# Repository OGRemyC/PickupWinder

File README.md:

View this project on [CADLAB.io](https://cadlab.io/project/1237). 

# PickupWinder
Arduino code designed to run on the Digispark Pro board.

Current Features:
<ul>
<li>Basic DC motor control</li>
<li>Open loop speed control</li>
</ul>

Future Features:
<ul>
<li>Full bi-directional control via H-bridge</li>
<li>Tachometer</li>
<li>Closed-loop speed control</li>
</ul>

Possible Extended Features:
<ul>
<li>Automatic tensioner</li>
<li>Closed loop wire tensioner</li>
<li>Linear spool positioning via lead screw</li>
<li>Automatic wrap with various profiles</li>
</ul>

<h1>Installation</h1>
<h2>Windows</h2>
Follow instructions from the <a href="https://digistump.com/wiki/digispark/tutorials/connectingpro">Digistrump Wiki</a>.
In addition, download and install the <a href="https://github.com/micronucleus">Micronucleus</a> bootloader driver installer.

<h3>Key Elements</h3>
<ul>
<li>Arduino 1.6.6 or newer</li>
<li>Digistump <a href="https://github.com/digistump/DigistumpArduino/releases/download/1.6.7/DigistumpDrivers.zip">Drivers</a></li>
<li>Micronucleus driver installer</li>
</ul>

<h3>Steps</h3>
<ol>
<li>Download Digistrump drivers, micronucleus, and Arduino.
<li>Install Arduino.</li>
<li>Unzip Digistump drivers and micronucleus to the Arduino sketchbook folder.</li>
<li>Run [Sketchbook]\micronucleus-master\windows_driver_installer\zadig_2.1.2.exe</li>
<li>In Zadig select Device>Load Preset Device. </li>
<li>Select micronucleus.cfg in the same folder. </li>
</ol>

<h1>Uploading Sketches to the DigiSpark Pro</h1>
Open \\PickupWinder\digiProPickupWinder\digiProPickupWinder.ino in the Arduino IDE.
Select "Digispark Pro (Default 16 MHz)" from Tools>Board:
Start click Upload.
Connect the DigiSpark board via USB

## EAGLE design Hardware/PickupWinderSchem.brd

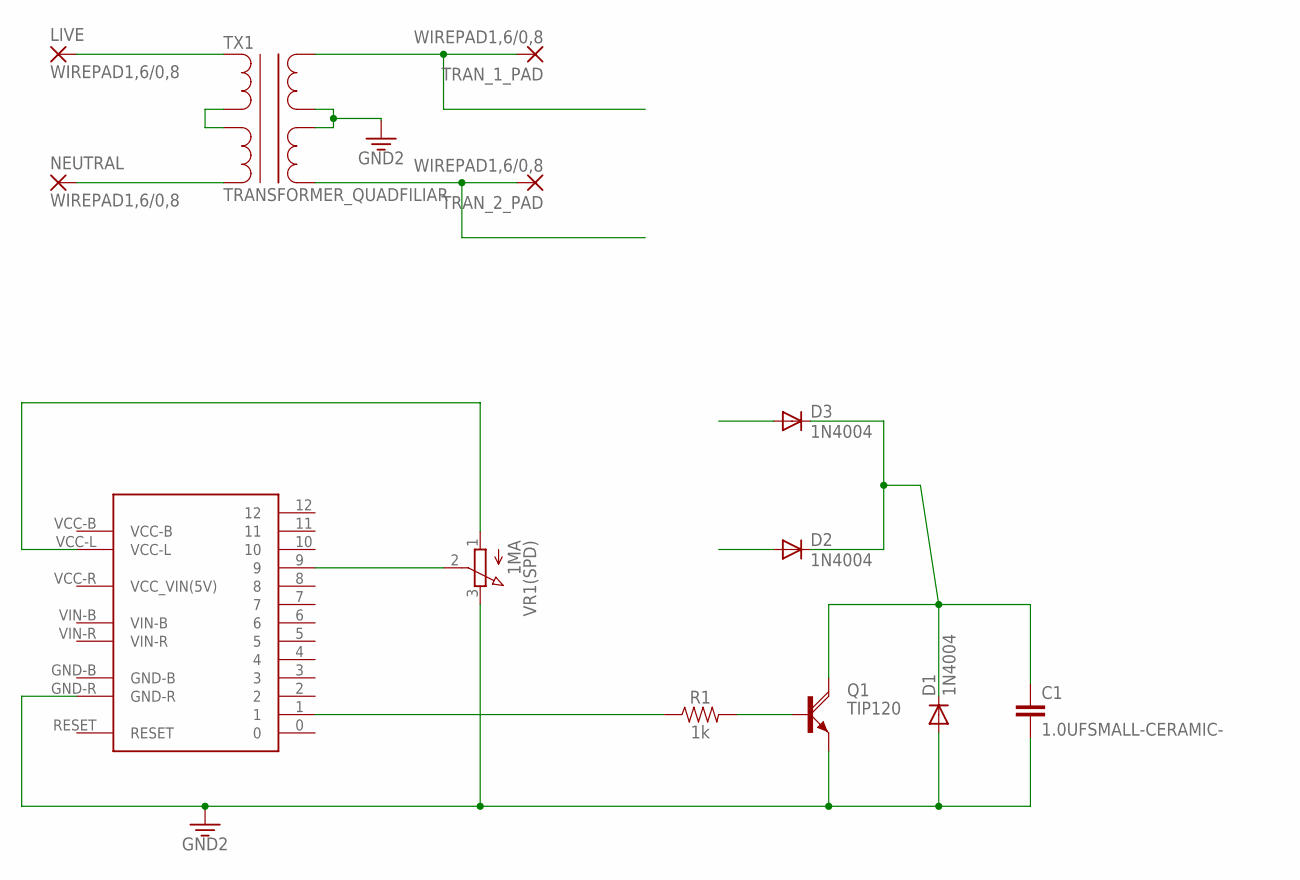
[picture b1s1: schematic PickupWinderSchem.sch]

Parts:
C1: 1.0UFSMALL-CERAMIC-; CERAMIC_SML
D1, D2, D3: 1N4004; DO41-10
LIVE: WIREPAD1,6/0,8; 1,6/0,8
NEUTRAL: WIREPAD1,6/0,8; 1,6/0,8
Q1: TIP120; TO220AH
R1: 1k; AXIAL-0.3
TRAN_1_PAD, TRAN_2_PAD: WIREPAD1,6/0,8; 1,6/0,8
TX1: TRANSFORMER_QUADFILIAR; COILCRAFT_DA230X
U$1: DIGISPARK_PRO
VR1(SPD): 1MA; 3RP/1610N

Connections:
3.3V: C1.P$2 (2), D1.A, Q1.E, U$1.GND-R, VR1(SPD).3 (E)
unnamed: R1.P$1 (1), U$1.1
unnamed: Q1.B, R1.P$2 (2)
unnamed: U$1.9, VR1(SPD).2 (S)
unnamed: U$1.VCC-L, VR1(SPD).1 (A)
unnamed: TX1.P$2 (2), TX1.P$3 (3)
unnamed: TX1.P$6 (6), TX1.P$7 (7)
unnamed: C1.P$1 (1), D1.C, D2.C, D3.C, Q1.C
unnamed: LIVE.1, TX1.P$4 (4)
unnamed: NEUTRAL.1, TX1.P$1 (1)
TRANS_1: D3.A, TRAN_1_PAD.1, TX1.P$8 (8)
TRANS_2: D2.A, TRAN_2_PAD.1, TX1.P$5 (5)

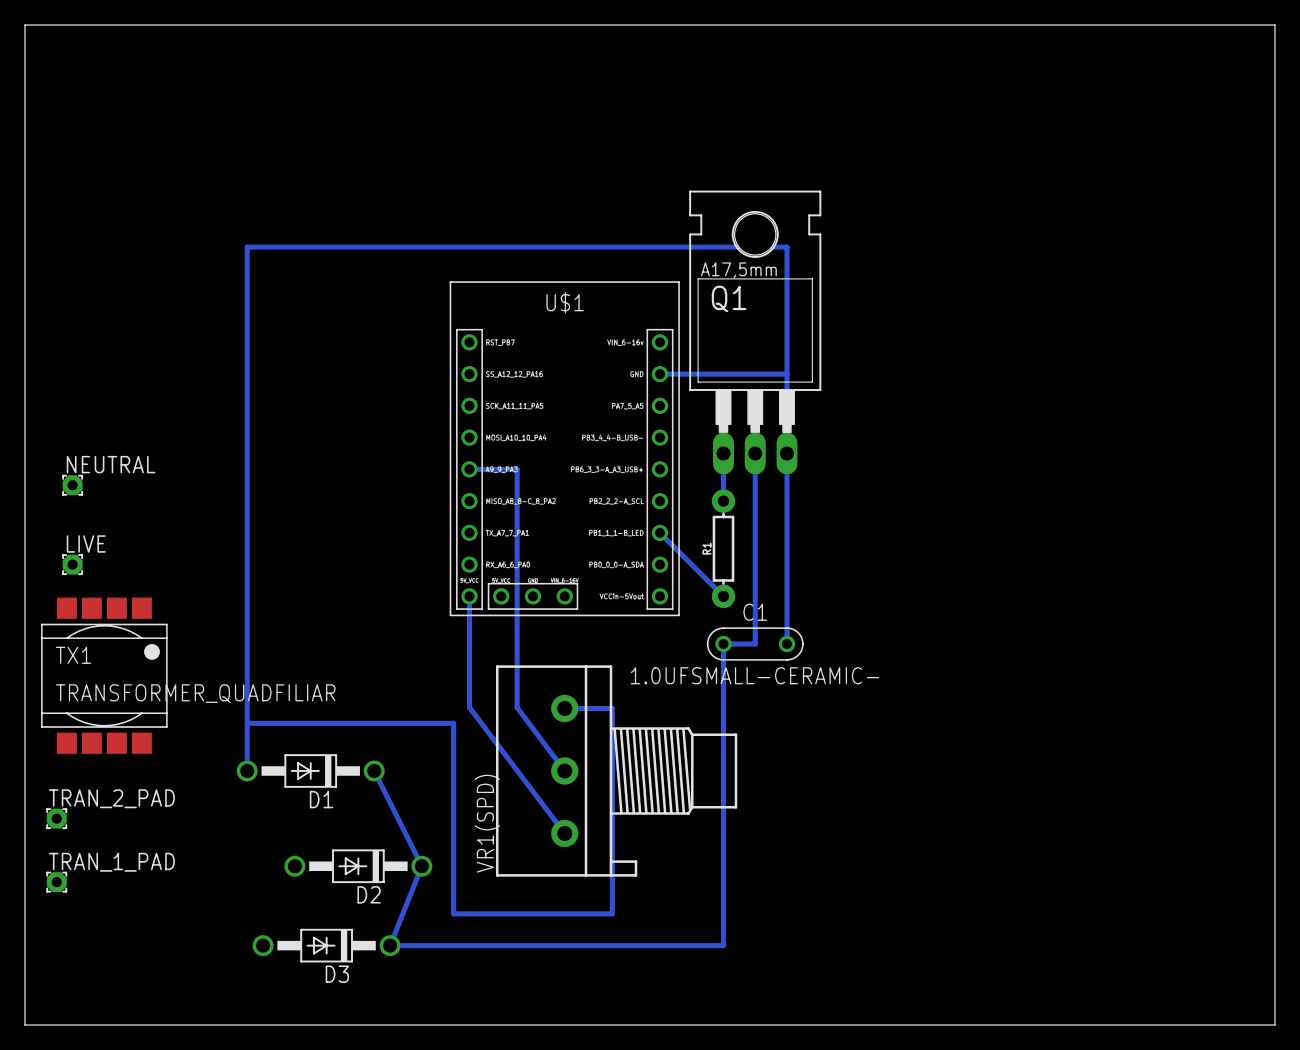
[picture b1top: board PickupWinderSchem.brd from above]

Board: 2 copper layers, 100.0 x 80.0 mm, 13 parts (0 on the bottom side), 12 nets.

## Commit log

2017-02-21 Add control sketch
    Basic prototyping has been underway. Current functionality includes:
    - PWM drive output
    - Open loop speed control via potentiometer
    - Basic prototyping with PWM registers (TCCRA/B)
    - Noticable changes in performance. Experiment with o'scope to confirm PWM characteristics
2017-02-21 Update README.md
    Add basic information about current and future functionality at time of initial code upload.
2017-02-21 Move sket to nested folder
    Prompted by Arduino IDE that the sketch needed to be inside a folder
    named digiProPickupWinder. The folder was created and the sketch was
    moved.
2017-02-22 Windows setup and upload process to Readme.md
    Added basic setup instructions for installing and connecting to the DIgispark Pro. WIndows process only. Basic outline of the upload added.
2017-02-22 Fixed install list
    forgot the close the tag for the install steps. closed the ol tag to set the upload apart as new section.
2017-03-07 Initial Schem and Layout
    First draft of the current darlinton transistor implementation.
2018-07-27 Backlink to CADLAB.io has been added.

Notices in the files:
parts and their libraries:
SparkFun-Capacitors: Licensing: Creative Commons ShareAlike 4.0 International - https://creativecommons.org/licenses/by-sa/4.0
